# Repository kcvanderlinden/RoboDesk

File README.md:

# RoboDesk
Read LOGICDATA protocol to control height of a powered sit/stand desk.

LOGICDATA protocol decoding from [phord's RoboDesk](https://github.com/phord/RoboDesk/tree/LogicData)

# Setup
Make sure to rename all *.example files and adjust variables, as of now we have:
* firmware/platformio.ini.example
* firmware/src/Credentials.h.example
* firmware/src/pins.h.example
* firmware/src/Wificonfig.h.example (optional)

## Features:
* Double tap a direction to go to a hardcoded target height
* Leverage MQTT to get / set height
  * Subscribed topics:
    * `<MQTT_TOPIC>/set` > e.g. `90` (sets the table height to 90 cm)
    * `<MQTT_TOPIC>/cmd` > ...
      * `up` (moves the table to the predefined high position `highTarget`)
      * `down` (moves the table to the predefined low position `lowTarget`)
      * `stop` (stops the table immediately)
      * `ping` (answers with `pong` on the same topic)
  * Published topics:
    * `<MQTT_TOPIC>/state` (up/down/stopped)
    * `<MQTT_TOPIC>/height` (height in cm)
    * `<MQTT_TOPIC>/button` (single/double up/down)
    * `<MQTT_TOPIC>/lastConnected` (will set and retained on connect with current version / build number)

## Files:
* `firmware`: platformio code for the d1 mini
* `schematic`: kicad schematic for the connections between the d1 mini and the desk
  * Two different but similar versions: `desk-schematic` and `Layout-Wemos-ProtoBoard`
* `schematic\case\robodesk-case.scad`: Enclosure using https://www.thingiverse.com/thing:1264391
* `images\logicdata-controller.xcf`: orthorectified top and bottom image of the logicdata controller `SMART-e-2-UNL-US`

## Hardware
* [Wemos/LOLIN D1 mini](https://www.wemos.cc/en/latest/d1/d1_mini.html)
* [Wemos ProtoBoard Shield](https://www.wemos.cc/en/latest/d1_mini_shield/protoboard.html)
* 2x 10kΩ pull-down resistors
* Circular DIN 7P male & female connectors
* 3PDT On-On switch (e.g. MIYAMA MS 500M-B)

## Links
* Blog post for [version 1](https://github.com/mtfurlan/RoboDesk/releases/tag/v1.0.0): https://technicallycompetent.com/hacking-logicdata-desk/
* Blog post for [version 2](https://github.com/mtfurlan/RoboDesk/releases/tag/v2.0.0): https://technicallycompetent.com/logicdata-desk-v2/

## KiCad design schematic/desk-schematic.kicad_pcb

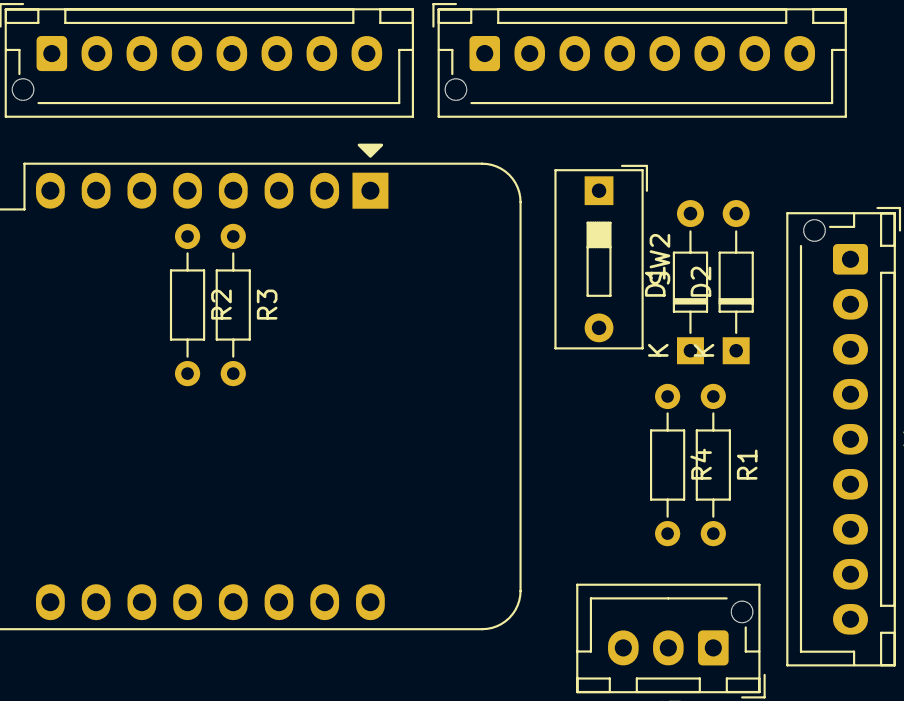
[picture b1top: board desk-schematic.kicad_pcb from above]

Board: 2 copper layers, 12 parts (0 on the bottom side), 17 nets, no tracks yet.

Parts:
ButtonConnector1: DIN-7-GND; JST_XH_B8B-XH-AM_1x08_P2.50mm_Vertical
D1, D2: D; D_DO-34_SOD68_P7.62mm_Horizontal
DeskConnector1: DIN-7-GND; JST_XH_B8B-XH-AM_1x08_P2.50mm_Vertical
J1: Conn_01x09; JST_XH_B9B-XH-AM_1x09_P2.50mm_Vertical
J3: Conn_01x03; JST_XH_B3B-XH-AM_1x03_P2.50mm_Vertical
R1, R2, R3, R4: R; R_Axial_DIN0204_L3.6mm_D1.6mm_P7.62mm_Horizontal
SW2: SW_DIP_x01; SW_DIP_SPSTx01_Slide_9.78x4.72mm_W7.62mm_P2.54mm
U1: WeMos_D1_mini; WEMOS_D1_mini_light

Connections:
+5V: ButtonConnector1.7, DeskConnector1.7, J1.1
/5V_SWITCHED: J1.8, R1.1, SW2.2
/ASSERT_DOWN: D2.2, J1.6, U1.13
/ASSERT_UP: D1.2, J1.3, U1.14
/BTN_DOWN: ButtonConnector1.5, J1.5, R3.1, U1.4
/BTN_UP: ButtonConnector1.3, J1.2, R2.1, U1.5
/CTL_DOWN: DeskConnector1.5, J1.7
/CTL_UP: DeskConnector1.3, J1.4
/HS3: ButtonConnector1.4, DeskConnector1.4
/HS4: ButtonConnector1.2, DeskConnector1.2
/PowerLED: J3.1, R1.2
/RxD: ButtonConnector1.1, DeskConnector1.1
/StatusLED: J3.2, R4.2
/TxD: ButtonConnector1.6, DeskConnector1.6, U1.6
GND: ButtonConnector1.8, DeskConnector1.8, J1.9, J3.3, R2.2, R3.2, U1.10
unnamed: D1.1, D2.1, R4.1
unnamed: SW2.1, U1.9

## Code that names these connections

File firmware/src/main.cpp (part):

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
const uint32_t debounce_time = 50;
const uint32_t double_time = 500;
int btn_pins[] = {BTN_UP, BTN_DOWN};
const int btn_pressed_state = HIGH;// when high, button is pressed

#define ARRAY_SIZE(array) (sizeof(array) / sizeof(array[0]))
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void setup() {

  // BTN_UP/DOWN are the physical buttons
  pinMode(BTN_UP, INPUT);
  pinMode(BTN_DOWN, INPUT);
  pinMode(LOGICDATA_RX, INPUT);

  // ASSERT_UP/DOWN are the connections to the motor
  pinMode(ASSERT_UP, OUTPUT);
  pinMode(ASSERT_DOWN, OUTPUT);

  Log.Init(LOG_LEVEL_DEBUG, 115200L);
  Log.Info(CR "---------" CR);
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
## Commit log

2022-05-11 Updated schematic to v2
2022-05-11 Links to the accompanying blog posts
2022-05-11 Added Wifi & MQTT
    * Credentials are configured in Credentials.h
    * Networking settings such as DNS, Gateway can be configured in Wificonfig.h
    * Example MQTT message is published on connection as well as button presses
2022-05-11 Set baud rate because default is 9600
2022-05-11 Enable setting height via MQTT
    Use by setting <topic>/set to a numeric value between minHeight and maxHeight.
    The table will continue until the target height is met.
2022-05-11 Added OTA firmware update
2022-05-11 Cleanup
    * renamed height to currentHeight
    * renamed target to targetHeight
    * renamed move() to move_table()
    * Externalized initMQTT for readability
    * Deprecated ICACHE_RAM_ATTR for IRAM_ATTR
2022-05-11 Added pins.h.example so pins.h may be private
2022-05-15 decrease mqtt message spam
2022-05-15 Move platformio.ini to example, readme setup changes
2022-05-15 Move phord's LogicData decoder to private lib
2022-05-16 Added logging library, better direction state, incoming comands
2022-05-16 handle min/max height
2022-05-16 refactoring
2022-05-16 Remove latches - everything can be done with setHeight
2022-05-17 added Fritzing shield layout, files cleanup
2022-05-17 logging simplification
2022-05-20 Got rid of latching, can all be done with setHeight
    * Code cleanup
    * Logging cleanup
2022-05-20 Added the switch as proposed in v2
2024-01-08 Copy of local pre-fork changes
